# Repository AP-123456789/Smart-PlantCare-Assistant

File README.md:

# Smart Plant Care Assistant

The **Smart Plant Care Assistant** is a plant-monitoring system built around the Seeed Studio XIAO RP2040 microcontroller. It monitors soil moisture, ambient temperature, and humidity, presenting real-time telemetry on an SSD1306 OLED display with visual status alerts via red and green LEDs. A push-button switch allows seamless navigation between multiple display pages.

## Project Design & Development Overview

1. **Schematic & Component Selection:** Designed in KiCad using the Seeed Studio XIAO RP2040 core. Wired analog soil moisture sensing, shared I2C bus lines for the AHT20 sensor and SSD1306 OLED display, dual-LED indicators with current-limiting resistors, and a debounced push button.

2. **Rules Checking & Footprints:** Configured `PWR_FLAG` symbols and No Connect markers to pass KiCad Electrical Rules Check (ERC) with zero errors. Mapped custom physical footprints for all surface-mount and through-hole components.
   
<br>

3. **PCB Layout & Routing:** Built a dual-layer PCB with routed power, ground, and signal traces, decoupling capacitors (`C1`, `C2`), and clean `Edge.Cuts` boundary outlines. Cleared all 19 Design Rules Check (DRC) clearance and text height warnings.

   <br>

5. **Manufacturing Preparation:** Generated and verified production Gerber layers, Excellon drill files, and 3D render outputs using KiCad Gerber Viewer.

6 . **Firmware Development:** Written in C++ using Visual Studio Code and PlatformIO under the Arduino framework. Integrated Adafruit driver libraries (`AHTX0`, `SSD1306`, `GFX`), implemented low moisture (<30%) and high temp (>35°C) alert logic, and added multi-page OLED UI toggling.

## Key Features

* **Microcontroller Core:** Seeed Studio XIAO RP2040 running custom C++/Arduino firmware developed in Visual Studio Code with PlatformIO.

* **Environmental Sensing:** High-precision ambient temperature and humidity tracking via the I2C AHT20 sensor.

* **Soil Moisture Monitoring:** Capacitive soil moisture sensor for corrosion-free analog measurement.

* **Multi-Page Visual Display:** 128x64 SSD1306 OLED displaying soil status on Page 1 and climate telemetry on Page 2.

* **User Interface Control:** Physical push button connected to interrupt input (`D3`) for instantaneous display page toggling.

* **Status Alert Logic:** Dynamic red/green LED indicators evaluating threshold conditions (low moisture <30%, high temp >35°C, dry air <30%).

* **Custom PCB Design:** Two-layer custom PCB designed in KiCad, complete with power decoupling capacitors and optimized trace routing.

## Bill of Materials (BOM)

All electronic components, hardware, and prototyping boards are sourced from a single vendor (**Adafruit**) to eliminate extra shipping fees and streamline procurement under \$30.00.

| Item No. | Component Description | Designator | Qty | Unit Price (\$) | Ext. Price (\$) | Vendor | Sourcing Link | 
| ----- | ----- | ----- | ----- | ----- | ----- | ----- | ----- | 
| **1** | Seeed Studio XIAO RP2040 Microcontroller | U1 | 1 | \$5.40 | \$5.40 | Adafruit | [Adafruit Product 5395](https://www.adafruit.com/product/5395) | 
| **2** | AHT20 Temperature & Humidity Sensor | J1 | 1 | \$4.50 | \$4.50 | Adafruit | [Adafruit Product 4566](https://www.adafruit.com/product/4566) | 
| **3** | SSD1306 OLED Display (128x64, I2C) | J2 | 1 | \$3.50 | \$3.50 | Adafruit | [Adafruit Product 938](https://www.adafruit.com/product/938) | 
| **4** | Capacitive Soil Moisture Sensor | J3 | 1 | \$4.95 | \$4.95 | Adafruit | [Adafruit Product 4026](https://www.adafruit.com/product/4026) | 
| **5** | Red LED (5mm) | D1 | 1 | \$0.25 | \$0.25 | Adafruit | [Adafruit Product 298](https://www.adafruit.com/product/298) | 
| **6** | Green LED (5mm) | D2 | 1 | \$0.25 | \$0.25 | Adafruit | [Adafruit Product 300](https://www.adafruit.com/product/300) | 
| **7** | 220 Ω Through-Hole Resistors | R1, R2 | 2 | \$0.10 | \$0.20 | Adafruit | [Adafruit Product 2780](https://www.adafruit.com/product/2780) | 
| **8** | Tactile Push Button Switch | SW1 | 1 | \$0.50 | \$0.50 | Adafruit | [Adafruit Product 367](https://www.adafruit.com/product/367) | 
| **9** | 100 nF Non-Polarized Capacitor | C1 | 1 | \$0.20 | \$0.20 | Adafruit | [Adafruit Product 2778](https://www.adafruit.com/product/2778) | 
| **10** | 10 µF Polarized Capacitor | C2 | 1 | \$0.25 | \$0.25 | Adafruit | [Adafruit Product 2195](https://www.adafruit.com/product/2195) | 
| **11** | Perma-Proto Custom PCB Board | PCB | 1 | \$2.95 | \$2.95 | Adafruit | [Adafruit Product 1609](https://www.adafruit.com/product/1609) | 

## Hardware Pinout and Schematic Mapping

| Microcontroller Pin | Connected Hardware Component | Signals / Net Label | Function Description | 
| ----- | ----- | ----- | ----- | 
| **D0 / A0** | Capacitive Soil Moisture Sensor | `SOIL_ANALOG` | Analog moisture reading (ADC input) | 
| **D1** | Red LED (via 220 Ω resistor R1) | `LED_RED` | High-risk / Alert status indicator output | 
| **D2** | Green LED (via 220 Ω resistor R2) | `LED_GREEN` | Healthy status indicator output | 
| **D3** | Push Button Switch (SW1) | `BTN_PAGE` | Display page toggle (Internal pull-up) | 
| **D4** | AHT20 Sensor & SSD1306 OLED | `I2C_SDA` | Shared I2C Data Line | 
| **D5** | AHT20 Sensor & SSD1306 OLED | `I2C_SCL` | Shared I2C Clock Line | 
| **3.3V / GND** | Capacitors C1 (100nF) & C2 (10µF) | `3V3` / `GND` | Power rail decoupling and filtering | 

## Repository Structure

```
├── Hardware/
│   ├── Plant_Care.kicad_pro       # KiCad Project File
│   ├── Plant_Care.kicad_sch       # Schematic Layout
│   ├── Plant_Care.kicad_pcb       # Two-Layer PCB Layout
│   └── Gerbers/                   # Production-ready Gerber & Drill files
├── Firmware/
│   ├── platformio.ini             # PlatformIO Board & Library Dependencies
│   └── src/
│       └── main.cpp               # Microcontroller Firmware Source Code
├── Manufacturing/
│   └── Plant_Care_Gerbers.zip     # Consolidated fabrication archive
└── README.md                      # Project documentation
```

## Firmware Setup and Compilation

### Prerequisites

1. Install [Visual Studio Code](https://code.visualstudio.com/).

2. Install the **PlatformIO IDE** extension from the VS Code Marketplace.

### Build Instructions

1. Clone or download this repository.

2. Open the `Firmware` directory in VS Code via PlatformIO.

3. Verify library declarations in `platformio.ini`:

   ```ini
   [env:seeed_xiao_rp2040]
   platform = https://github.com/maxgerhardt/platform-raspberrypi.git
   board = seeed_xiao_rp2040
   framework = arduino
   lib_deps = 
       adafruit/Adafruit AHTX0 @ ^2.0.5
       adafruit/Adafruit SSD1306 @ ^2.5.7
       adafruit/Adafruit GFX Library @ ^1.11.5
   ```

4. Run the build command via terminal or PlatformIO toolbar:

   ```bash
   pio run
   ```

5. Connect the XIAO RP2040 via USB-C and flash the binary:

   ```bash
   pio run --target upload
   ```

## References

* [KiCad Official Documentation](https://www.kicad.org/documentation/)

* [Seeed Studio XIAO RP2040 Datasheet & Guide](https://wiki.seeedstudio.com/XIAO-RP2040/)

* [PlatformIO Raspberry Pi RP2040 Integration](https://docs.platformio.org/en/latest/platforms/raspberrypi.html)

* [Adafruit AHTX0 Driver Documentation](https://github.com/adafruit/Adafruit_AHTX0)

* [Adafruit SSD1306 Display Driver](https://github.com/adafruit/Adafruit_SSD1306)

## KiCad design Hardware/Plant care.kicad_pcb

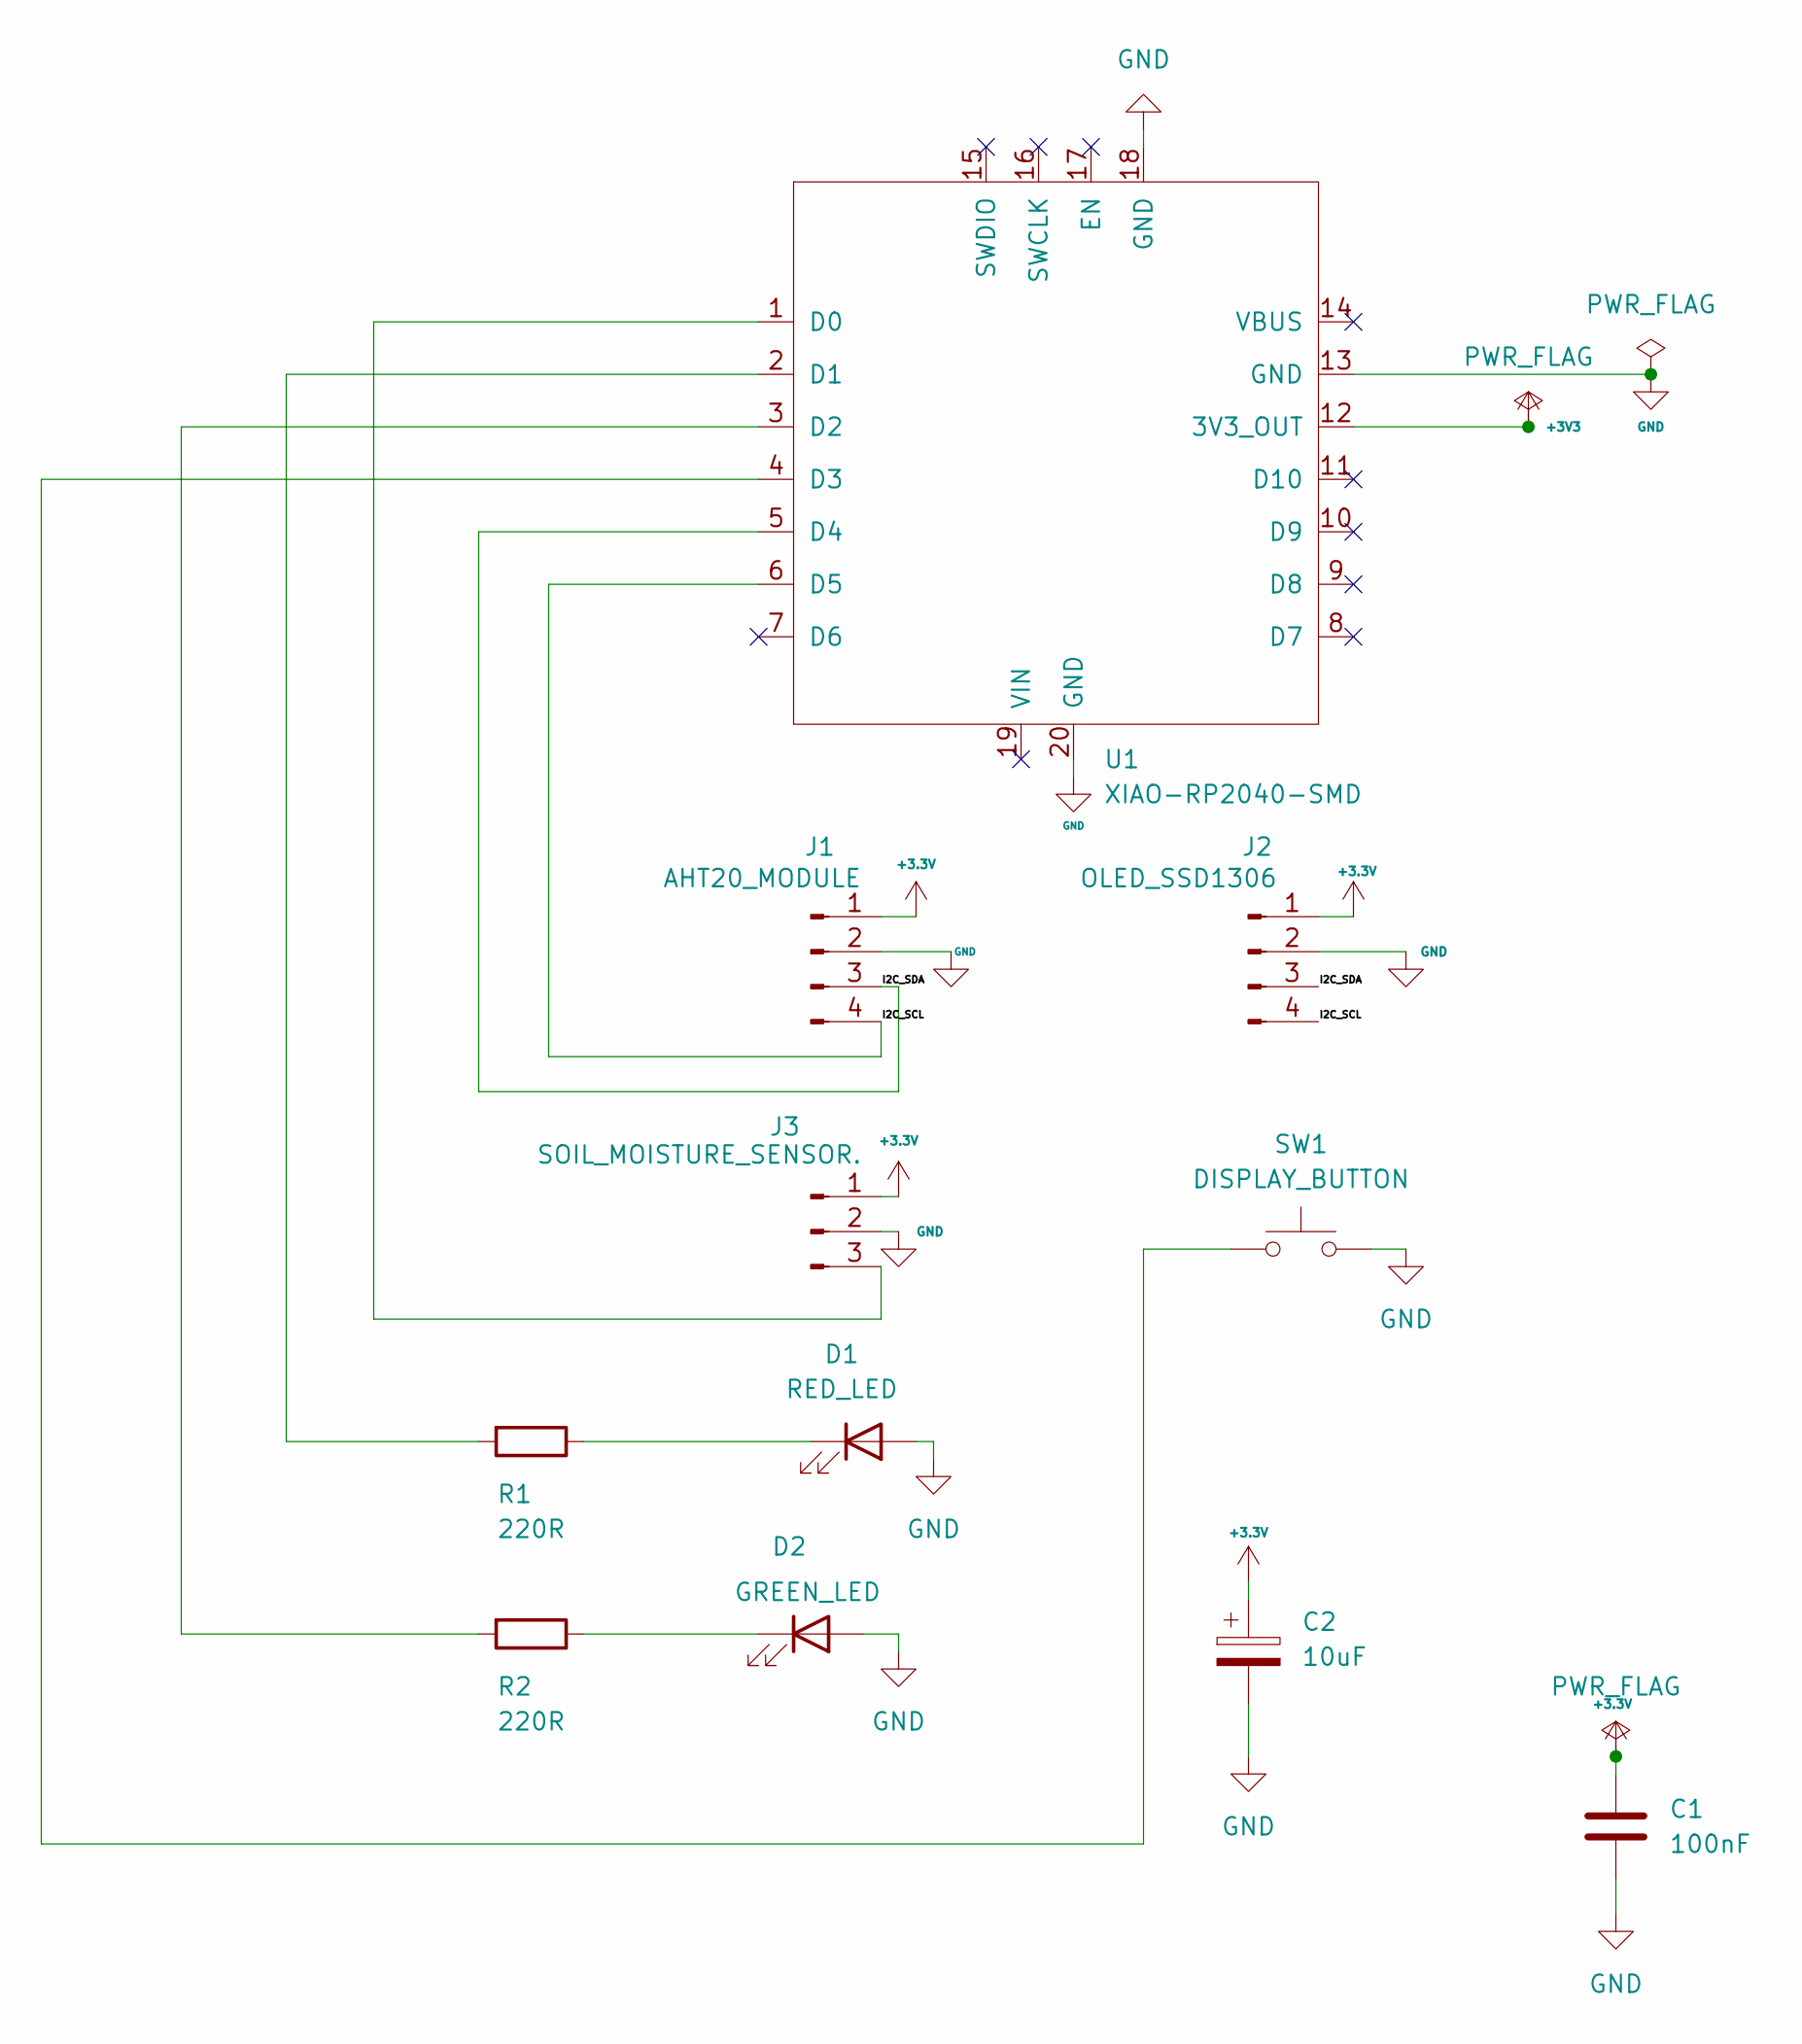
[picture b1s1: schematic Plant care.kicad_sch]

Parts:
C1: 100nF; C_Disc_D5.0mm_W2.5mm_P5.00mm
C2: 10uF; CP_Radial_D5.0mm_P2.50mm
D1: RED_LED; LED_D5.0mm
D2: GREEN_LED; LED_D5.0mm
J1: AHT20_MODULE; PinHeader_1x04_P2.54mm_Vertical
J2: OLED_SSD1306; PinHeader_1x04_P2.54mm_Vertical
J3: SOIL_MOISTURE_SENSOR.; PinHeader_1x03_P2.54mm_Vertical
R1, R2: 220R; R_Axial_DIN0207_L6.3mm_D2.5mm_P7.62mm_Horizontal
SW1: DISPLAY_BUTTON; SW_PUSH_6mm
U1: XIAO-RP2040-SMD

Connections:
+3.3V: C1.1, C2.1, J1.1, J2.1, J3.1
+3V3: U1.12 (3V3_OUT)
/I2C_SCL: J1.4, J2.4, U1.6 (D5)
/I2C_SDA: J1.3, J2.3, U1.5 (D4)
GND: C1.2, C2.2, D1.2 (A), D2.2 (A), J1.2, J2.2, J3.2, SW1.2, U1.13 (GND), U1.18 (GND), U1.20 (GND)
unnamed: D1.1 (K), R1.1
unnamed: D2.1 (K), R2.1
unnamed: J3.3, U1.1 (D0)
unnamed: R1.2, U1.2 (D1)
unnamed: R2.2, U1.3 (D2)
unnamed: SW1.1, U1.4 (D3)

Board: 2 copper layers, 11 parts (0 on the bottom side), 10 nets, no tracks yet.
